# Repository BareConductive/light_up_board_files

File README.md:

# Light Up Board CAD Files and Firmware

These are the CAD files and the firmware for the [Light Up Board](https://www.bareconductive.com/shop/light-up-board/).

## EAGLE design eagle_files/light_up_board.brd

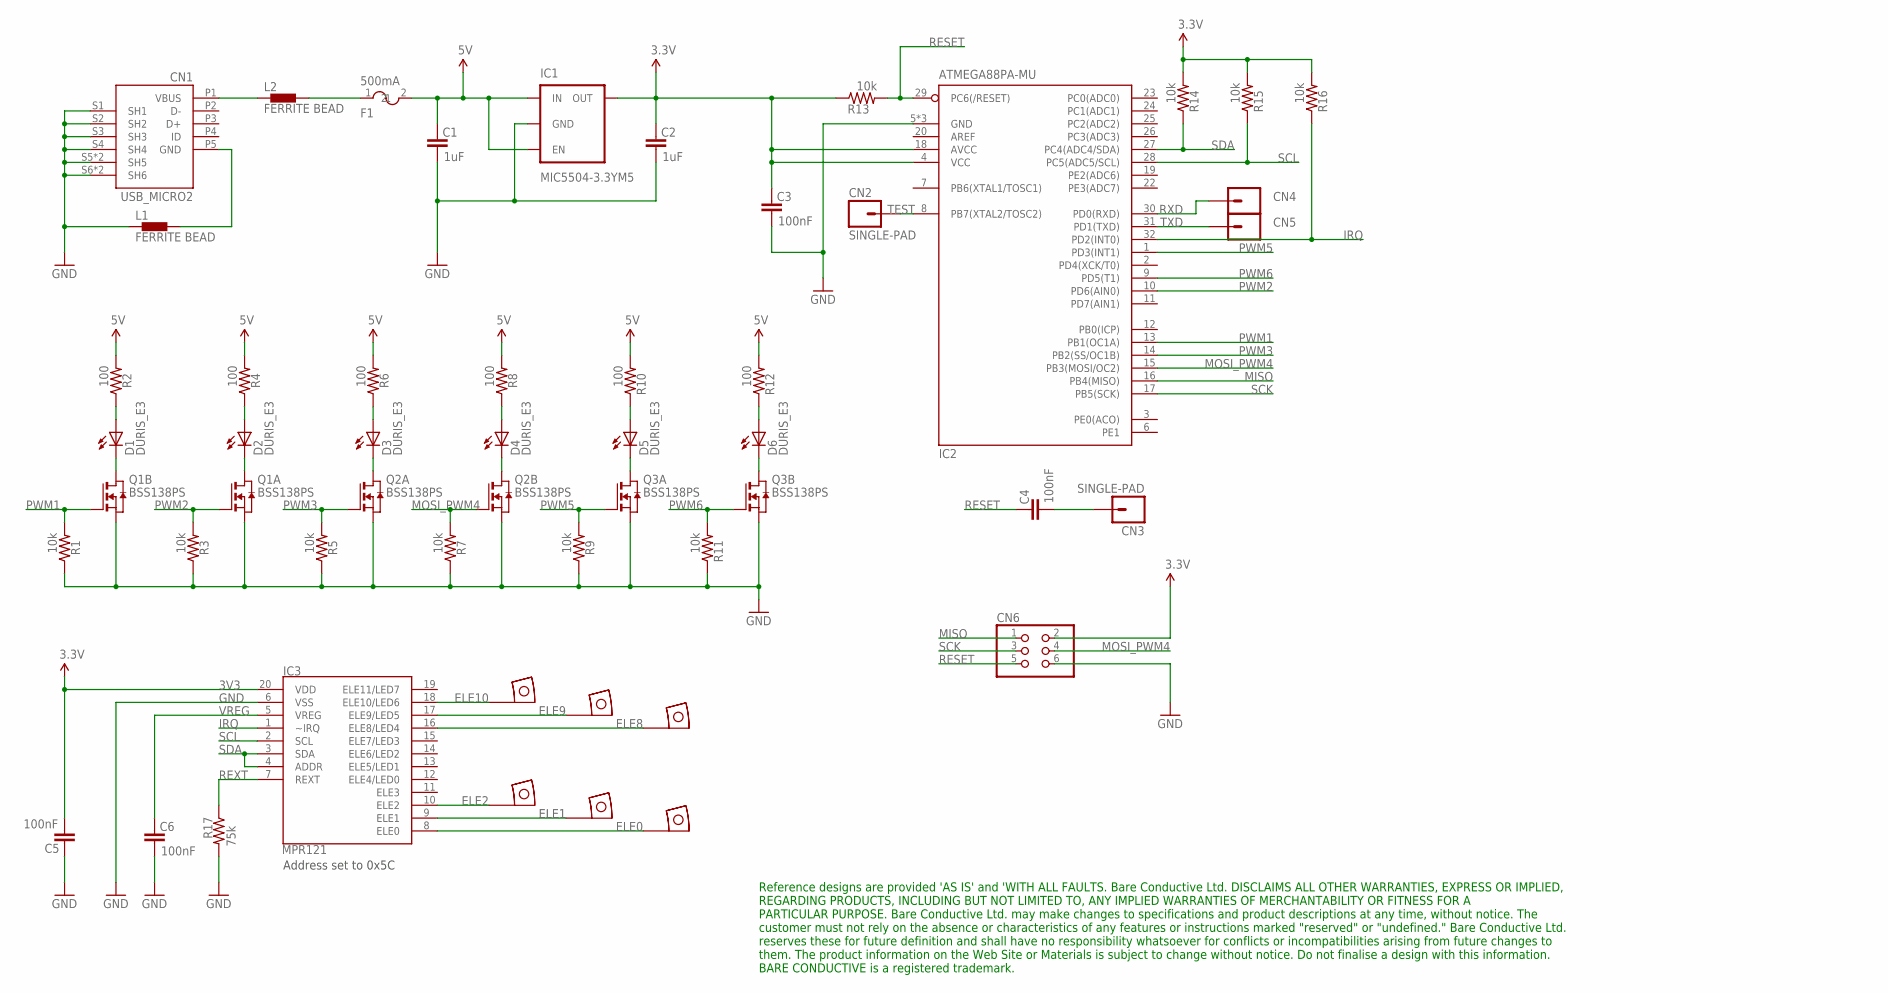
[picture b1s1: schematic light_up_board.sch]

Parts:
C1, C2: 1uF; 0402-CAP
C3, C4, C5, C6: 100nF; 0402-CAP
CN1: USB_MICRO2; USB_MICRO_B_SCK_2_TANGS
CN2, CN3, CN4, CN5: SINGLE-PAD; 1MM_0.4MM_DRILL_PAD
CN6: ICSP; 2X03_1.27_SQ1_0.4_DRILL
D1, D2, D3, D4, D5, D6: DURIS_E3; PLCC2_3X1.4
F1: 500mA; MF-PSMF050X-2
IC1: MIC5504-3.3YM5; SOT23-5
IC2: ATMEGA88PA-MU; HVQFN32-MEDPADS
IC3: MPR121; QFN-20-0.4MM-LONGPADS-NORESIST
L1, L2: FERRITE BEAD; 0402
Q1, Q2, Q3: BSS138PS; SOT363_PHILIPS
R1, R3, R5, R7, R9, R11, R13, R14, R15, R16: 10k; 0402-RES
R2, R4, R6, R8, R10, R12: 100; 0402-RES
R17: 75k; 0402-RES
U$1, U$2, U$3, U$4, U$5, U$6: EPSK-ELEC_2.0; EPSK_ELEC_2.0

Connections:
3V3: C2.2, C3.2, C5.1, CN6.2, IC1.5 (OUT), IC2.4 (VCC), IC2.18 (AVCC), IC3.20 (VDD), R13.1, R14.2, R15.2, R16.2
5V: C1.2, F1.2, IC1.1 (IN), IC1.3 (EN), R2.2, R4.2, R6.2, R8.2, R10.2, R12.2
ELE0: IC3.8 (ELE0), U$6.1
ELE1: IC3.9 (ELE1), U$4.1
ELE2: IC3.10 (ELE2), U$2.1
ELE8: IC3.16 (ELE8/LED4), U$5.1
ELE9: IC3.17 (ELE9/LED5), U$3.1
ELE10: IC3.18 (ELE10/LED6), U$1.1
GND: C1.1, C2.1, C3.1, C5.2, C6.1, CN1.S1 (SH1), CN1.S2 (SH2), CN1.S3 (SH3), CN1.S4 (SH4), CN1.S5 (SH5), CN1.S6 (SH6), CN1.S7 (SH5), CN1.S8 (SH6), CN6.6, IC1.2 (GND), IC2.5 (GND), IC2.21 (GND), IC2.EXP (GND), IC3.6 (VSS), L1.1, Q1.1 (S), Q1.4 (S), Q2.1 (S), Q2.4 (S), Q3.1 (S), Q3.4 (S), R1.1, R3.1, R5.1, R7.1, R9.1, R11.1, R17.2
IRQ: IC2.32 (PD2(INT0)), IC3.1 (~IRQ), R16.1
MISO: CN6.1, IC2.16 (PB4(MISO))
MOSI_PWM4: CN6.4, IC2.15 (PB3(MOSI/OC2)), Q2.5 (G), R7.2
unnamed: D4.A, R8.1
unnamed: CN1.P1 (VBUS), L2.1
unnamed: D1.K (C), Q1.3 (D)
unnamed: CN1.P5 (GND), L1.2
unnamed: F1.1, L2.2
unnamed: C4.1, CN3.1
unnamed: D1.A, R2.1
unnamed: D5.A, R10.1
unnamed: D6.A, R12.1
unnamed: D2.K (C), Q1.6 (D)
unnamed: D2.A, R4.1
unnamed: D3.A, R6.1
unnamed: D3.K (C), Q2.6 (D)
unnamed: D4.K (C), Q2.3 (D)
unnamed: D5.K (C), Q3.6 (D)
unnamed: D6.K (C), Q3.3 (D)
PWM1: IC2.13 (PB1(OC1A)), Q1.5 (G), R1.2
PWM2: IC2.10 (PD6(AIN0)), Q1.2 (G), R3.2
PWM3: IC2.14 (PB2(SS/OC1B)), Q2.2 (G), R5.2
PWM5: IC2.1 (PD3(INT1)), Q3.2 (G), R9.2
PWM6: IC2.9 (PD5(T1)), Q3.5 (G), R11.2
RESET: C4.2, CN6.5, IC2.29 (PC6(/RESET)), R13.2
REXT: IC3.7 (REXT), R17.1
RXD: CN4.1, IC2.30 (PD0(RXD))
SCK: CN6.3, IC2.17 (PB5(SCK))
SCL: IC2.28 (PC5(ADC5/SCL)), IC3.2 (SCL), R15.1
SDA: IC2.27 (PC4(ADC4/SDA)), IC3.3 (SDA), IC3.4 (ADDR), R14.1
TEST: CN2.1, IC2.8 (PB7(XTAL2/TOSC2))
TXD: CN5.1, IC2.31 (PD1(TXD))
VREG: C6.2, IC3.5 (VREG)

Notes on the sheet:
Address set to 0x5C
Reference designs are provided 'AS IS' and 'WITH ALL FAULTS. Bare Conductive Ltd. DISCLAIMS ALL OTHER WARRANTIES, EXPRESS OR IMPLIED, REGARDING PRODUCTS, INCLUDING BUT NOT LIMITED TO, ANY IMPLIED WARRANTIES OF MERCHANTABILITY OR FITNESS FOR A PARTICULAR PURPOSE. Bare Conductive Ltd. may make change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

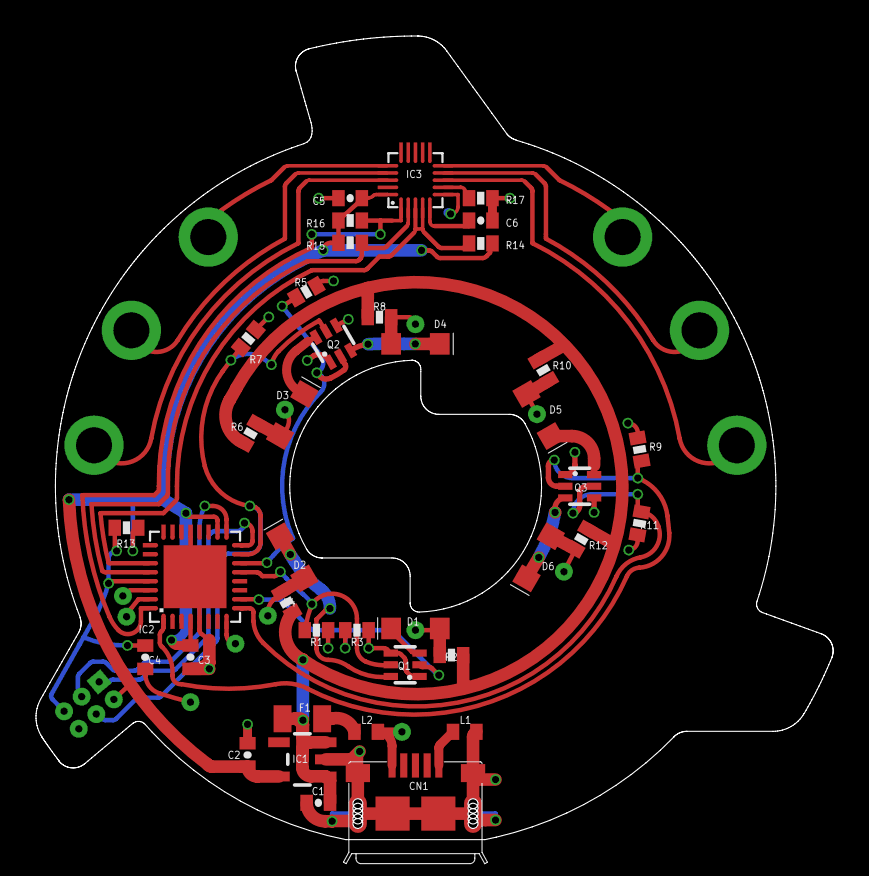
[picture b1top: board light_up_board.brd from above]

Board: 2 copper layers, 44.3 x 44.6 mm, 50 parts (0 on the bottom side), 42 nets.

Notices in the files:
parts and their libraries:
SparkFun-Aesthetics: Licensing: CC v3.0 Share-Alike You are welcome to use this library for commercial purposes.
